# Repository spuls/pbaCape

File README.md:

pbaCape
=======

BeagleBone Cape for pba ("Platz-Beregnungs-Anlage")

For software see https://github.com/fknittel/pba

## TestBoard
For testing the basic circuit a test layout was developed. It was soldered together and used with one original relay (same as used for the "real" thing).

## Prototype RC1
The RC1 schematics were send of for PCB manufacturing. The bare board was soldered manually. The prototype is still used for the "real" thing. But:
- Some resistor values were choosen borderline. Only 4 out of 6 outputs worked as advertised. (Values corrected in V05.sch)
  Wrong relay behaviour can be seen here: https://www.youtube.com/watch?v=9P7xhbd6JEQ 
  Correctly it should be: https://www.youtube.com/watch?v=5yiceOrfvFM 
- Some GPIOs (P8_39, 41, 43, 45) that were chosen first interfered with "boot"-pins of the BeagelBone. Thus, the board would not boot properly.
  These were manually corrected via wire bridges to be P8_17, 18, 28 and 30 respectively. (Also corrected in V05.sch)
- There is no internet connection (currently). Thus, no time information is available. A real time clock (RTC) was needed. It was manually soldered. 
  (Not yet corrected in schematics.)

## Code
The code here is only for simple testing purposes. It uses PyBBIO (https://github.com/alexanderhiam/PyBBIO/wiki).

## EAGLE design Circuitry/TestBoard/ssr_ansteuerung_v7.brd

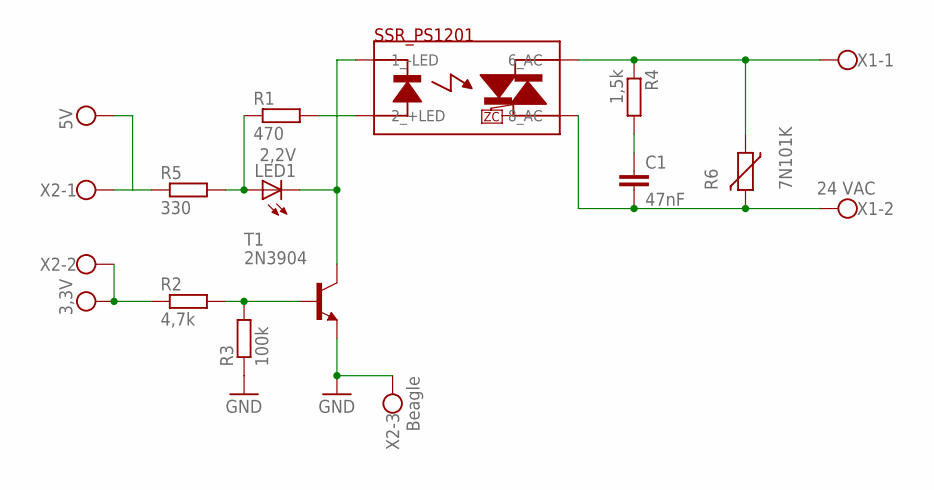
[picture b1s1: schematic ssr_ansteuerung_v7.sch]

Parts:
C1: 47nF; C7.5B3
LED1: 2,2V; LED5MM
R1: 470; 0204/7
R2: 4,7k; 0204/7
R3: 100k; 0204/7
R4: 1,5k; 0204/7
R5: 330; 0204/7
R6: 7N101K; R-5
SSR_PS1201: SSR PS1201; S202S02
T1: 2N3904; TO92
X1: 24 VAC; W237-102
X2: Beagle; W237-103

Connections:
GND: R3.1, T1.3 (E), X2.3
unnamed: R1.2, SSR_PS1201.2 (2_+LED)
unnamed: LED1.A, R1.1, R5.2
unnamed: R2.2, R3.2, T1.2 (B)
unnamed: LED1.K (C), SSR_PS1201.1 (1_-LED), T1.1 (C)
unnamed: C1.1, R4.2
unnamed: R4.1, R6.1, SSR_PS1201.6 (6_AC), X1.1
unnamed: C1.2, R6.2, SSR_PS1201.8 (8_AC), X1.2
unnamed: R5.1, X2.1
VCC: R2.1, X2.2

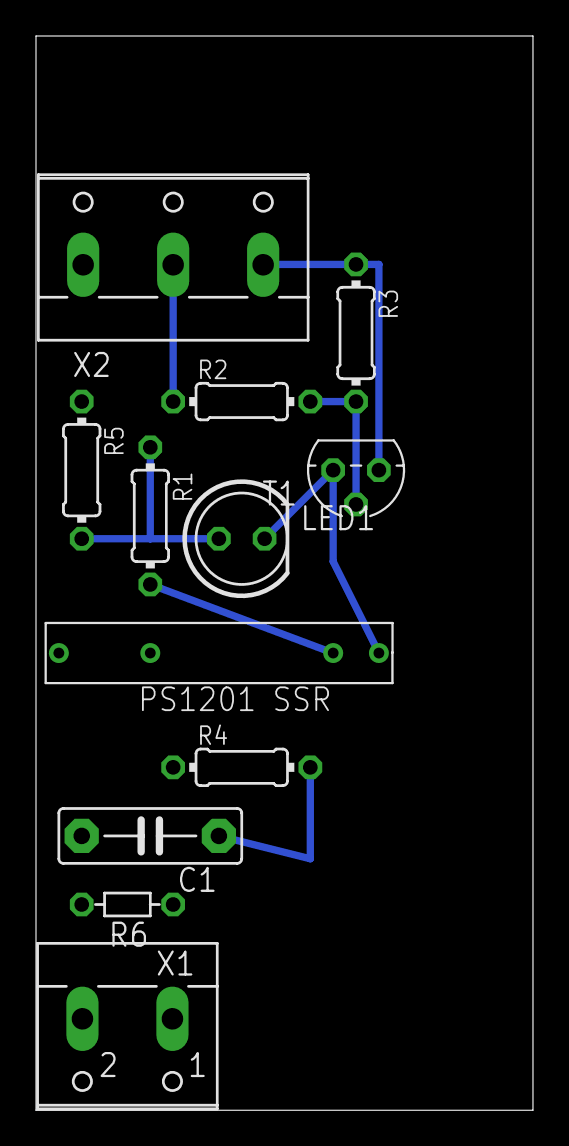
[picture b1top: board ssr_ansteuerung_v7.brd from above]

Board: 2 copper layers, 27.6 x 59.7 mm, 12 parts (0 on the bottom side), 10 nets.

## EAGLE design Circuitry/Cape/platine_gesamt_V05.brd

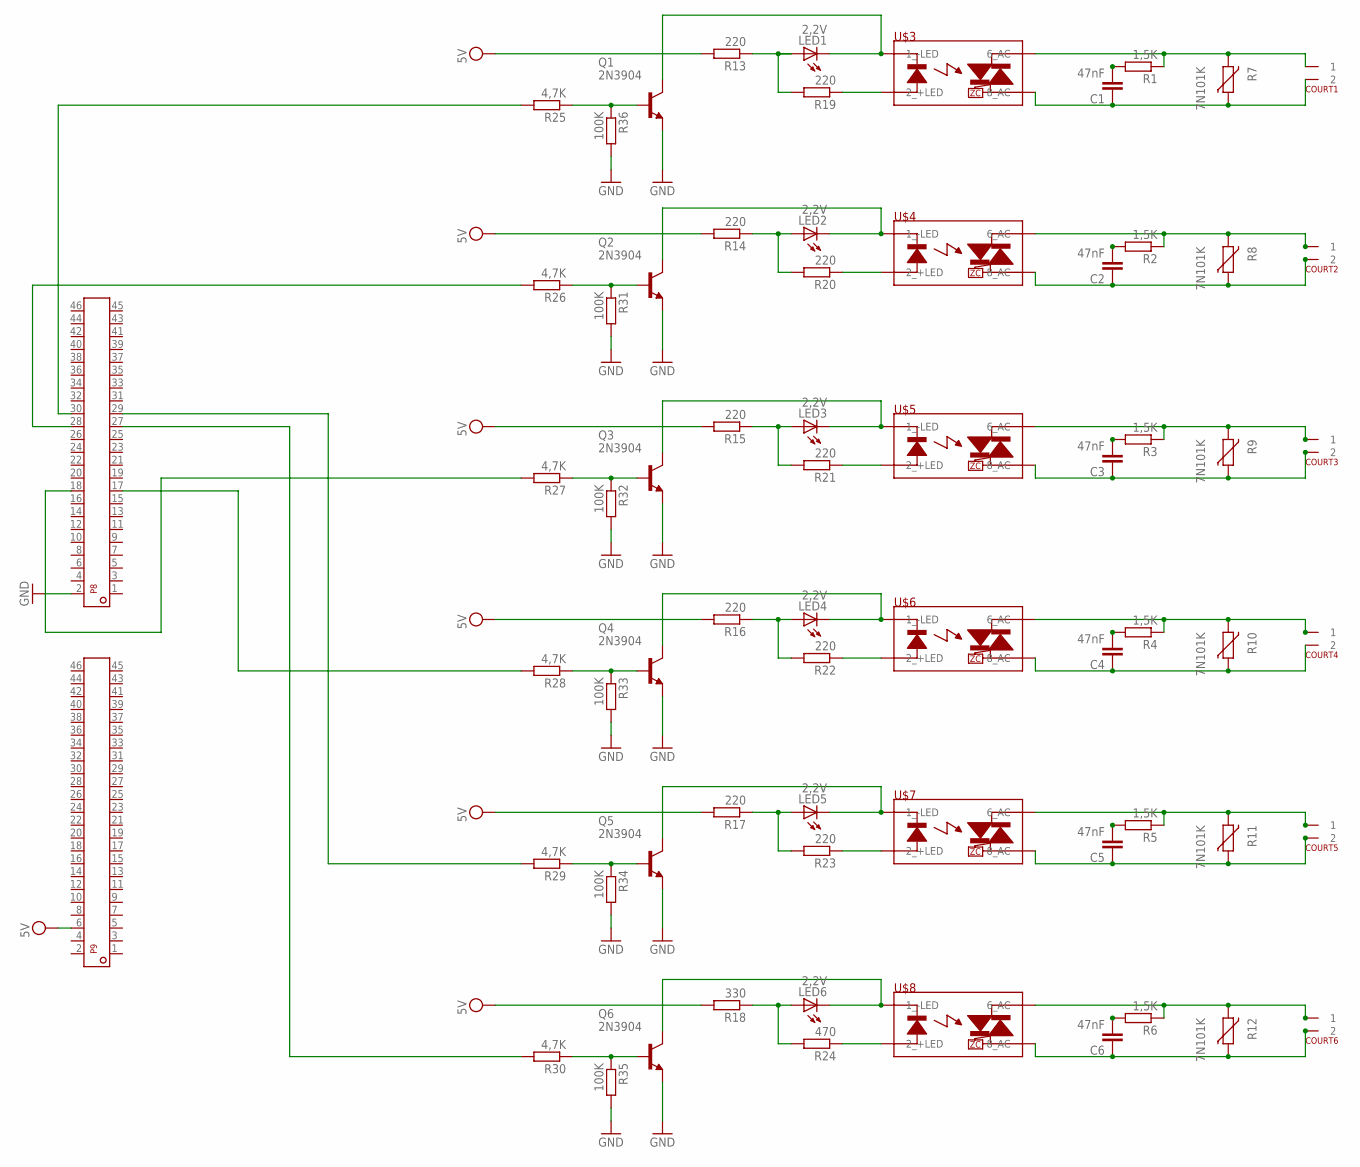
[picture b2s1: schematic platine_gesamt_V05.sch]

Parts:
C1, C2, C3, C4, C5, C6: 47nF; C7.5B3
COURT1, COURT2, COURT3, COURT4, COURT5, COURT6: KLEMMENBLOCK_2POL
LED1, LED2, LED3, LED4, LED5, LED6: 2,2V; LED5MM
P8, P9: FEMALE_HEADER_2X23; FE23-2W
Q1, Q2, Q3, Q4, Q5, Q6: 2N3904; TO92
R1, R2, R3, R4, R5, R6: 1,5K; 0204/7
R7, R8, R9, R10, R11, R12: 7N101K; R-5
R13, R14, R15, R16, R17, R19, R20, R21, R22, R23: 220; 0204/7
R18: 330; 0204/7
R24: 470; 0204/7
R25, R26, R27, R28, R29, R30: 4,7K; 0204/7
R31, R32, R33, R34, R35, R36: 100K; 0204/7
U$3, U$4, U$5, U$6, U$7, U$8: IXYS_PS1201_SSRSIP4/8; S202S02

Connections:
GND: P8.2, Q1.3 (E), Q2.3 (E), Q3.3 (E), Q4.3 (E), Q5.3 (E), Q6.3 (E), R31.2, R32.2, R33.2, R34.2, R35.2, R36.2
unnamed: C1.2, R1.2
unnamed: C2.2, R2.2
unnamed: C3.2, R3.2
unnamed: C4.2, R4.2
unnamed: C5.2, R5.2
unnamed: C6.2, R6.2
unnamed: COURT1.1, R1.1, R7.2, U$3.6 (6_AC)
unnamed: P8.18, R27.2
unnamed: C2.1, COURT2.2, R8.1, U$4.8 (8_AC)
unnamed: C3.1, COURT3.2, R9.1, U$5.8 (8_AC)
unnamed: C4.1, COURT4.2, R10.1, U$6.8 (8_AC)
unnamed: C5.1, COURT5.2, R11.1, U$7.8 (8_AC)
unnamed: C6.1, COURT6.2, R12.1, U$8.8 (8_AC)
unnamed: COURT2.1, R2.1, R8.2, U$4.6 (6_AC)
unnamed: COURT3.1, R3.1, R9.2, U$5.6 (6_AC)
unnamed: COURT4.1, R4.1, R10.2, U$6.6 (6_AC)
unnamed: COURT5.1, R5.1, R11.2, U$7.6 (6_AC)
unnamed: COURT6.1, R6.1, R12.2, U$8.6 (6_AC)
unnamed: LED1.A, R13.1, R19.2
unnamed: R19.1, U$3.2 (2_+LED)
unnamed: LED1.K (C), Q1.1 (C), U$3.1 (1_-LED)
unnamed: Q1.2 (B), R25.1, R36.1
unnamed: LED2.A, R14.1, R20.2
unnamed: R20.1, U$4.2 (2_+LED)
unnamed: LED2.K (C), Q2.1 (C), U$4.1 (1_-LED)
unnamed: Q2.2 (B), R26.1, R31.1
unnamed: LED3.A, R15.1, R21.2
unnamed: R21.1, U$5.2 (2_+LED)
unnamed: LED3.K (C), Q3.1 (C), U$5.1 (1_-LED)
unnamed: Q3.2 (B), R27.1, R32.1
unnamed: LED4.A, R16.1, R22.2
unnamed: LED4.K (C), Q4.1 (C), U$6.1 (1_-LED)
unnamed: R22.1, U$6.2 (2_+LED)
unnamed: Q4.2 (B), R28.1, R33.1
unnamed: LED5.A, R17.1, R23.2
unnamed: LED5.K (C), Q5.1 (C), U$7.1 (1_-LED)
unnamed: R23.1, U$7.2 (2_+LED)
unnamed: Q5.2 (B), R29.1, R34.1
unnamed: LED6.A, R18.1, R24.2
unnamed: LED6.K (C), Q6.1 (C), U$8.1 (1_-LED)
unnamed: R24.1, U$8.2 (2_+LED)
unnamed: Q6.2 (B), R30.1, R35.1
unnamed: P8.30, R25.2
unnamed: P8.28, R26.2
unnamed: P8.17, R28.2
unnamed: P8.29, R29.2
unnamed: P8.27, R30.2
unnamed: C1.1, COURT1.2, R7.1, U$3.8 (8_AC)
VDD: P9.6, R13.2, R14.2, R15.2, R16.2, R17.2, R18.2

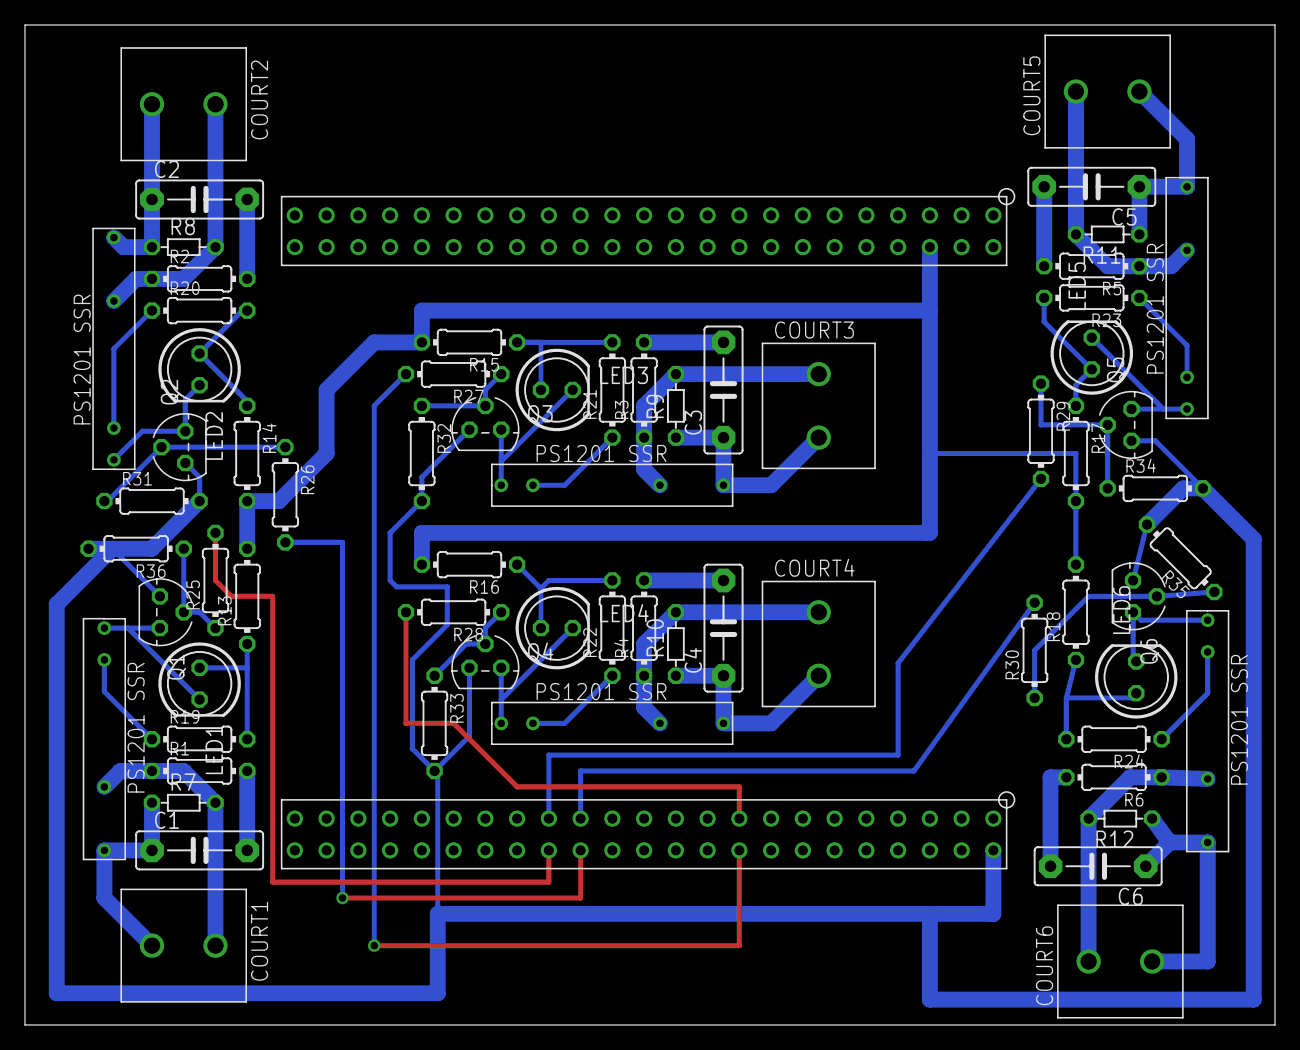
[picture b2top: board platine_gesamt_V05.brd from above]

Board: 2 copper layers, 100.0 x 80.0 mm, 68 parts (0 on the bottom side), 50 nets.

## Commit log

2014-10-30 :neckbeard: Added .gitattributes & .gitignore files
2014-10-30 added link to pba software to readme
2014-10-30 all files added
    All files for schematics, data sheets etc added.
2014-10-30 more info in readme
